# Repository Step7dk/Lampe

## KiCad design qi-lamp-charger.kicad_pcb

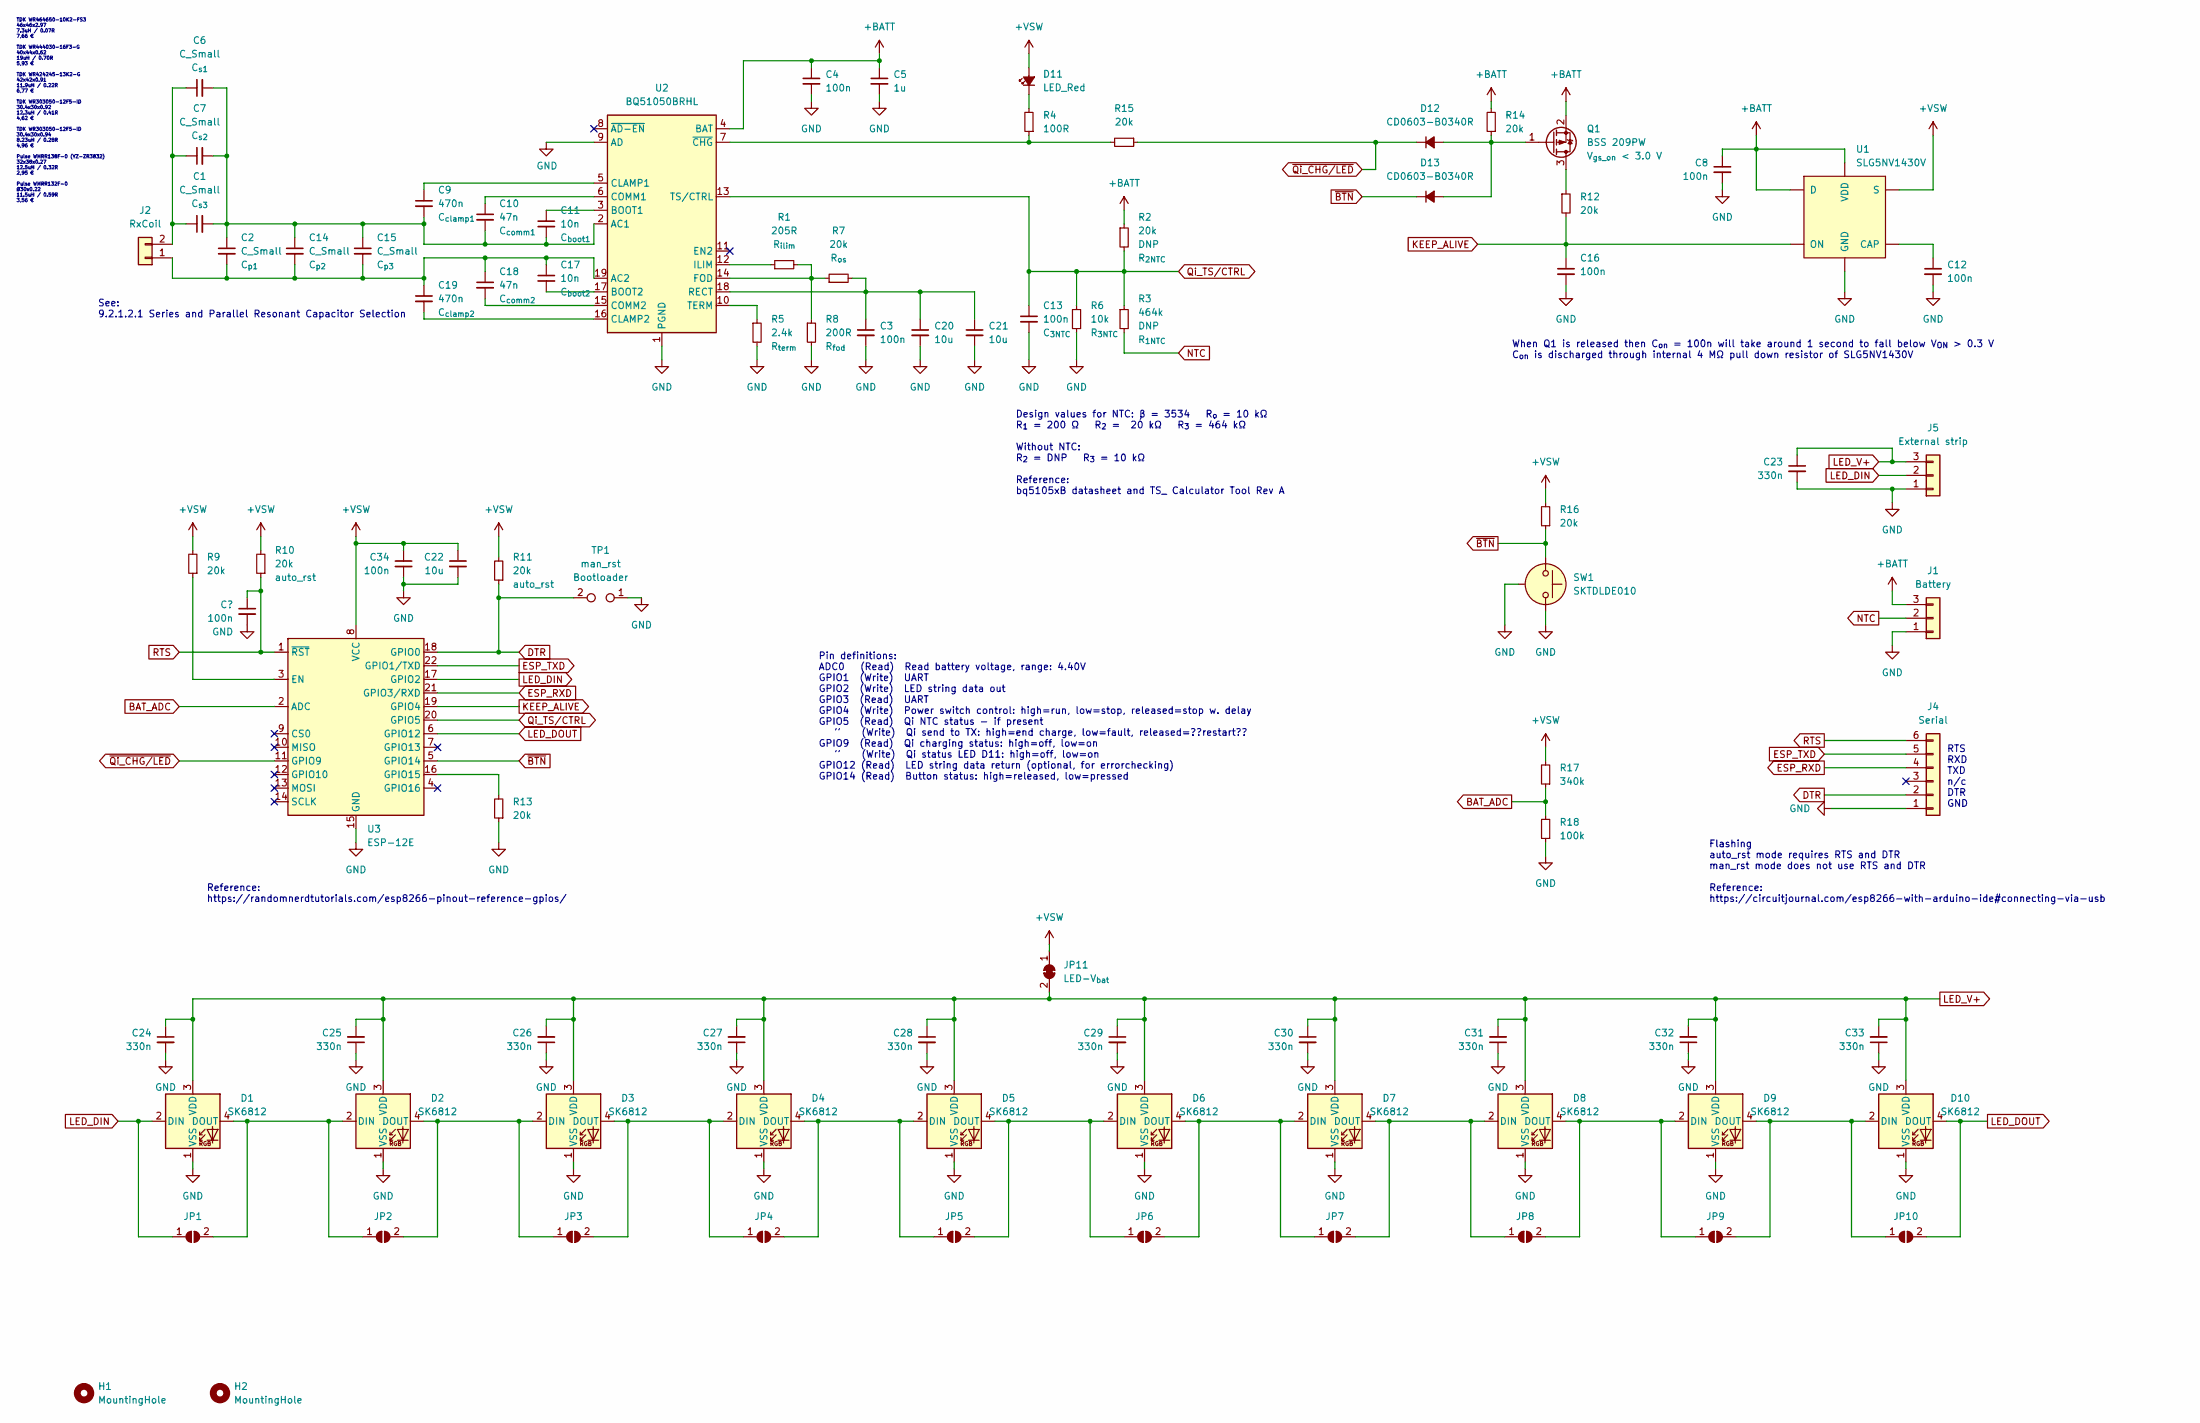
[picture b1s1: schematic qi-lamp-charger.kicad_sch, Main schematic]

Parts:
C1, C2, C6, C7, C14, C15: C_Small; C_0603_1608Metric; Rating 50V
C3, C4, C8, C12, C13, C16, C34: 100n; C_0603_1608Metric; Manufacturer_Part_Number CL10B104KO8NNND
C5: 1u; C_0603_1608Metric; Manufacturer_Part_Number CL10A105KO8NNNC
C9, C19: 470n; C_0603_1608Metric; Manufacturer_Part_Number CL10B474KO8NNNC
C10, C18: 47n; C_0603_1608Metric; Manufacturer_Part_Number CL10B473KO8NNND
C11, C17: 10n; C_0603_1608Metric; Manufacturer_Part_Number CL10B103KO8NNNC
C20, C21, C22: 10u; C_0805_2012Metric; Manufacturer_Part_Number CL21A106KOQNNNE
C23, C24, C25, C26, C27, C28, C29, C30, C31, C32, C33: 330n; C_0603_1608Metric; Manufacturer_Part_Number CL10B334KO8NNNC
D1, D2, D3, D4, D5, D6, D7, D8, D9, D10: SK6812; LED_SK6812_PLCC4_5.0x5.0mm_P3.2mm; Manufacturer_Part_Number SK6812
D11: LED_Red; LED_0603_1608Metric; Manufacturer_Part_Number LTST-C191KFKT
D12, D13: CD0603-B0340R; D_0603_1608Metric; Manufacturer_Part_Number CD0603-B0340R
H1, H2: MountingHole; MountingHole_2.2mm_M2
J1, J5: Conn_01x03; PinHeader_1x03_P2.54mm_Vertical
J2: Conn_01x02; PinHeader_1x02_P2.54mm_Vertical
J4: Conn_01x06; PinHeader_1x06_P2.54mm_Vertical
JP1, JP2, JP3, JP4, JP5, JP6, JP7, JP8, JP9, JP10: SolderJumper_2_Open; SolderJumper-2_P1.3mm_Open_RoundedPad1.0x1.5mm
JP11: SolderJumper_2_Bridged; SolderJumper-2_P1.3mm_Bridged_RoundedPad1.0x1.5mm
Q1: BSS 209PW; SOT-23; Rating V_{gs_on} < 3.0 V; Manufacturer_Part_Number BSS209PWH6327XTSA1
R1: 205R; R_0603_1608Metric; Manufacturer_Part_Number ERJ-3EKF2050V
R2, R7, R9, R10, R11, R12, R13, R14, R15, R16: 20k; R_0603_1608Metric; Manufacturer_Part_Number ERJ-3EKF2002V
R3: 464k; R_0603_1608Metric; Manufacturer_Part_Number ERJ-3EKF4643V
R4: 100R; R_0603_1608Metric; Manufacturer_Part_Number ERJ-3EKF1000V
R5: 2.4k; R_0603_1608Metric; Manufacturer_Part_Number ERJ-3EKF2401V
R6: 10k; R_0603_1608Metric; Manufacturer_Part_Number ERJ-3EKF1002V
R8: 200R; R_0603_1608Metric; Manufacturer_Part_Number ERJ-3EKF2000V
R17: 340k; R_0603_1608Metric; Manufacturer_Part_Number ERJ-3EKF3403V
R18: 100k; R_0603_1608Metric; Manufacturer_Part_Number ERJ-3EKF1003V
SW1: SKTDLDE010; Manufacturer_Part_Number SKTDLDE010
TP1: TestPoint_2Pole; PinHeader_1x02_P1.27mm_Vertical
U1: SLG5NV1430V; TDFN-8_1.5x2.0mm_P0.5mm (Fused Lead); Manufacturer_Part_Number SLG5NV1430V
U2: BQ51050BRHL; Texas_VQFN-RHL-20; Manufacturer_Part_Number BQ51050BRHLR
U3: ESP-12E

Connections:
+BATT: C4.1, C5.1, C8.1, J1.3, Q1.2 (S), R2.1, R14.2, U1.1 (VDD), U1.3 (D), U1.4 (D), U2.4 (BAT)
+VSW: C22.1, C34.1, D11.2 (A), JP11.1 (A), R9.2, R10.2, R11.2, R16.2, R17.2, U1.5 (S), U1.6 (S), U3.8 (VCC)
BAT_ADC: R17.1, R18.2, U3.2 (ADC)
DTR: J4.2, R11.1, TP1.2, U3.18 (GPIO0)
ESP_RXD: J4.4, U3.21 (GPIO3/RXD)
ESP_TXD: J4.5, U3.22 (GPIO1/TXD)
GND: C3.2, C4.2, C5.2, C8.2, C12.2, C13.2, C16.2, C20.2, C21.2, C22.2, C23.2, C24.2, C25.1, C26.1, C27.1, C28.2, C29.2, C30.2, C31.1, C32.1, C33.1, C34.2, D1.1 (VSS), D2.1 (VSS), D3.1 (VSS), D4.1 (VSS), D5.1 (VSS), D6.1 (VSS), D7.1 (VSS), D8.1 (VSS), D9.1 (VSS), D10.1 (VSS), J1.1, J4.1, J5.1, R5.2, R6.2, R8.2, R13.1, R18.1, SW1.1, SW1.3, TP1.1, U1.8 (GND), U2.1 (PGND), U2.9 (AD), U2.20 (PGND), U2.21 (PGND), U3.15 (GND)
KEEP_ALIVE: C16.1, R12.2, U1.2 (ON), U3.19 (GPIO4)
LED_DIN: D1.2 (DIN), J5.2, JP1.1 (A), U3.17 (GPIO2)
LED_DOUT: D10.4 (DOUT), JP10.2 (B), U3.6 (GPIO12)
LED_V+: C23.1, C24.1, C25.2, C26.2, C27.2, C28.1, C29.1, C30.1, C31.2, C32.2, C33.2, D1.3 (VDD), D2.3 (VDD), D3.3 (VDD), D4.3 (VDD), D5.3 (VDD), D6.3 (VDD), D7.3 (VDD), D8.3 (VDD), D9.3 (VDD), D10.3 (VDD), J5.3, JP11.2 (B)
NTC: J1.2, R3.2
unnamed: C1.1, C6.1, C7.1, J2.2
unnamed: C1.2, C2.1, C6.2, C7.2, C9.2, C10.2, C11.2, C14.1, C15.1, U2.2 (AC1)
unnamed: C9.1, U2.5 (CLAMP1)
unnamed: C10.1, U2.6 (COMM1)
unnamed: C11.1, U2.3 (BOOT1)
unnamed: C12.1, U1.7 (CAP)
unnamed: C2.2, C14.2, C15.2, C17.1, C18.1, C19.1, J2.1, U2.19 (AC2)
unnamed: C17.2, U2.17 (BOOT2)
unnamed: C18.2, U2.15 (COMM2)
unnamed: C19.2, U2.16 (CLAMP2)
unnamed: C3.1, C20.1, C21.1, R7.2, U2.18 (RECT)
unnamed: D1.4 (DOUT), D2.2 (DIN), JP1.2 (B), JP2.1 (A)
unnamed: D2.4 (DOUT), D3.2 (DIN), JP2.2 (B), JP3.1 (A)
unnamed: D3.4 (DOUT), D4.2 (DIN), JP3.2 (B), JP4.1 (A)
unnamed: D4.4 (DOUT), D5.2 (DIN), JP4.2 (B), JP5.1 (A)
unnamed: D5.4 (DOUT), D6.2 (DIN), JP5.2 (B), JP6.1 (A)
unnamed: D6.4 (DOUT), D7.2 (DIN), JP6.2 (B), JP7.1 (A)
unnamed: D7.4 (DOUT), D8.2 (DIN), JP7.2 (B), JP8.1 (A)
unnamed: D8.4 (DOUT), D9.2 (DIN), JP8.2 (B), JP9.1 (A)
unnamed: D9.4 (DOUT), D10.2 (DIN), JP9.2 (B), JP10.1 (A)
unnamed: D11.1 (K), R4.2
unnamed: D12.2 (A), D13.2 (A), Q1.1 (G), R14.1
unnamed: Q1.3 (D), R12.1
unnamed: R1.1, U2.12 (ILIM)
unnamed: R1.2, R7.1, R8.1, U2.14 (FOD)
unnamed: R5.1, U2.10 (TERM)
unnamed: R9.1, U3.3 (EN)
unnamed: R13.2, U3.16 (GPIO15)
unnamed: R4.1, R15.2, U2.7 (~CHG)
Qi_TS/CTRL: C13.1, R2.2, R3.1, R6.1, U2.13 (TS/CTRL), U3.20 (GPIO5)
RTS: J4.6, R10.1, U3.1 (~RST)
~BTN: D13.1 (K), R16.1, SW1.2, U3.5 (GPIO14)
~Qi_CHG/LED: D12.1 (K), R15.1, U3.11 (GPIO9)

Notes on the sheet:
Reference: https://randomnerdtutorials.com/esp8266-pinout-reference-gpios/
TDK WR464650-10K2-FS3 46x46x2.97 7.3uH / 0.07R 7,66 € TDK WR444030-16F3-G 40x44x0.62 19uH / 0.70R 5,93 € TDK WR424245-13K2-G 42x42x0.91 11.9uH / 0.22R 6,77 € TDK WR303050-12F5-ID 30.4x30x0.92 12.3uH / 0.41R 4,62 € TDK WR303050-12F5-ID 30.4x30x0.94 8.23uH / 0.28R 4,96 € Pulse WMRR138F-0 (YZ-ZR3832) 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
Flashing auto_rst mode requires RTS and DTR man_rst mode does not use RTS and DTR Reference: https://circuitjournal.com/esp8266-with-arduino-ide#connecting-via-usb
Design values for NTC: β = 3534 R_{o} = 10 kΩ R_{1} = 200 Ω R_{2} = 20 kΩ R_{3} = 464 kΩ Without NTC: R_{2} = DNP R_{3} = 10 kΩ Reference: bq5105xB datasheet and TS_ Calculator Tool Rev A
See: 9.2.1.2.1 Series and Parallel Resonant Capacitor Selection
When Q1 is released then C_{on} = 100n will take around 1 second to fall below V_{ON} > 0.3 V C_{on} is discharged through internal 4 MΩ pull down resistor of SLG5NV1430V
RTS RXD TXD n/c DTR GND
Pin definitions: ADC0 (Read) Read battery voltage, range: 4.40V GPIO1 (Write) UART GPIO2 (Write) LED string data out GPIO3 (Read) UART GPIO4 (Write) Power switch control: high=run, low=stop, released=stop w. delay GPIO5 (Read) Qi NTC status - if present '' (Write) Qi send to TX: high=end charge, lo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

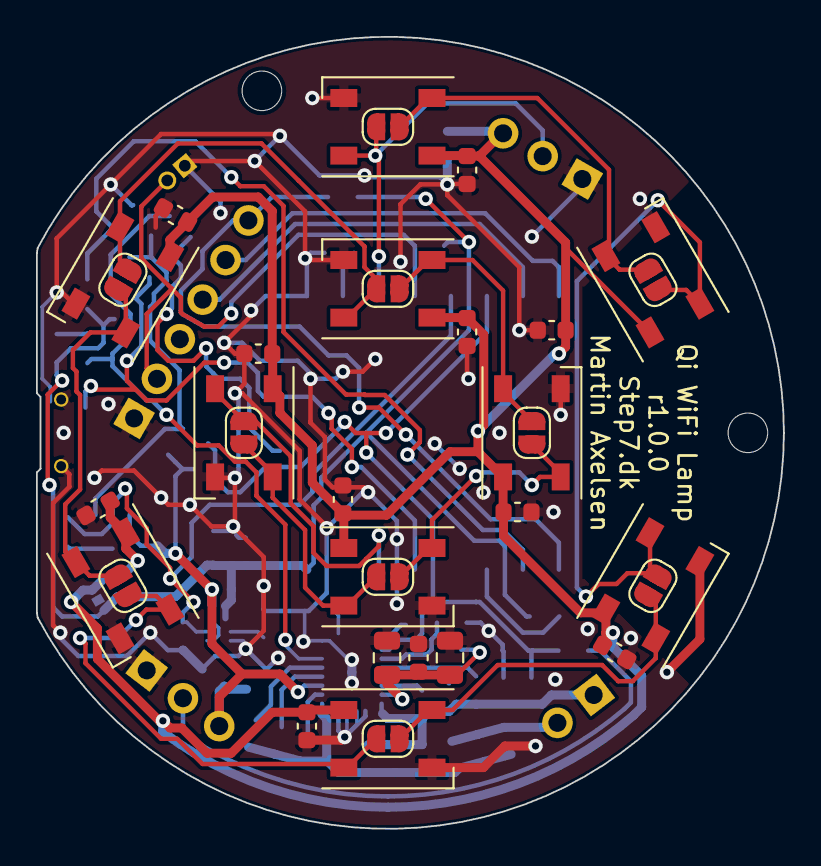
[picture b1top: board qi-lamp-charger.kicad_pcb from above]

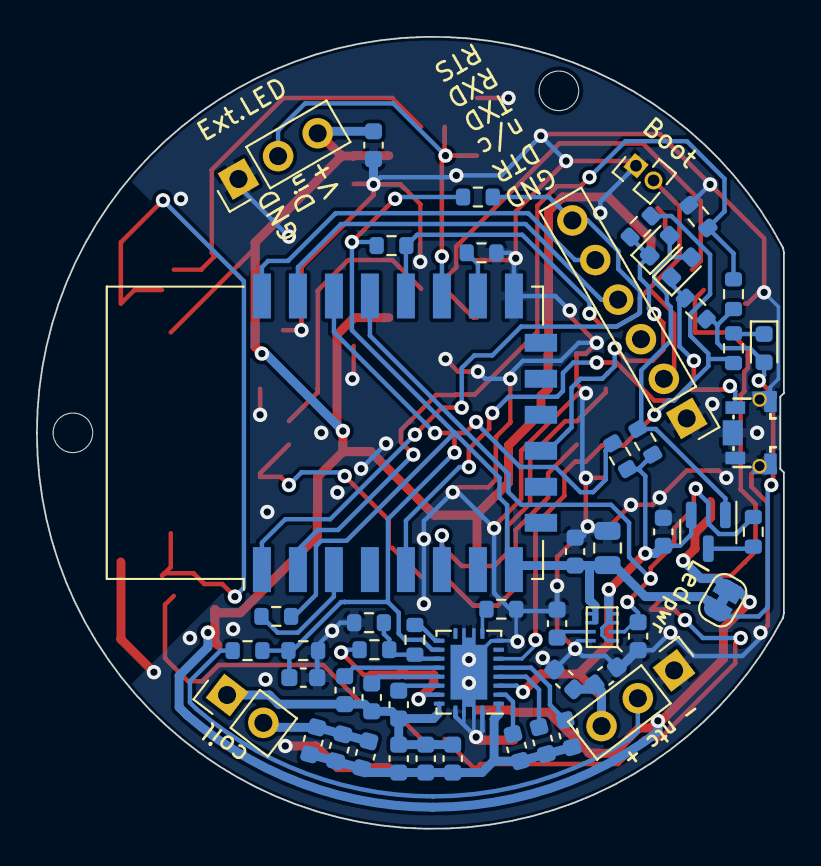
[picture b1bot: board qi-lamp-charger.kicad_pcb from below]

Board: 2 copper layers, 41.5 x 44.0 mm, 88 parts (53 on the bottom side), 45 nets.

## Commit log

2022-05-12 Set up Qi schematic
2022-05-12 rearrange
2022-05-12 add esp8266
2022-05-16 Add power switch & LED's & ESP_GPIO's
2022-05-16 Schematic done - missing just two footprints
2022-05-17 Redraw Button/DTR/GPIO0 complex & assign footprints
2022-05-17 Layout proposal 1
2022-05-18 Layout proposal 2
2022-05-18 Layout Qi
2022-05-18 Modules built
2022-05-18 Moving in
2022-05-19 Puzzling
2022-05-19 Puzzling #2
2022-05-19 Puzzling #3
2022-05-19 Puzzling #4
2022-05-19 Puzzle #4 - has GPIO0 brainfart
2022-05-20 Puzzle #5
2022-05-20 Shematic changed
2022-05-21 Minor corrections to layout (not up to date with previous commit)
2022-05-21 Puzzle #6
2022-05-22 Puzzle #7
2022-05-22 Puzzle complete incl. DRC
2022-05-23 Add info
2022-05-23 As ordered
2022-05-24 Add one chip 3D model
2022-06-03 PCBA r1.0 setup
2022-10-19 update pin description
2022-10-20 Corrections
2022-11-14 Improve text readability
2022-11-14 add reset cap in sch & bump to t1.0.999
2022-11-14 outline retract at button
